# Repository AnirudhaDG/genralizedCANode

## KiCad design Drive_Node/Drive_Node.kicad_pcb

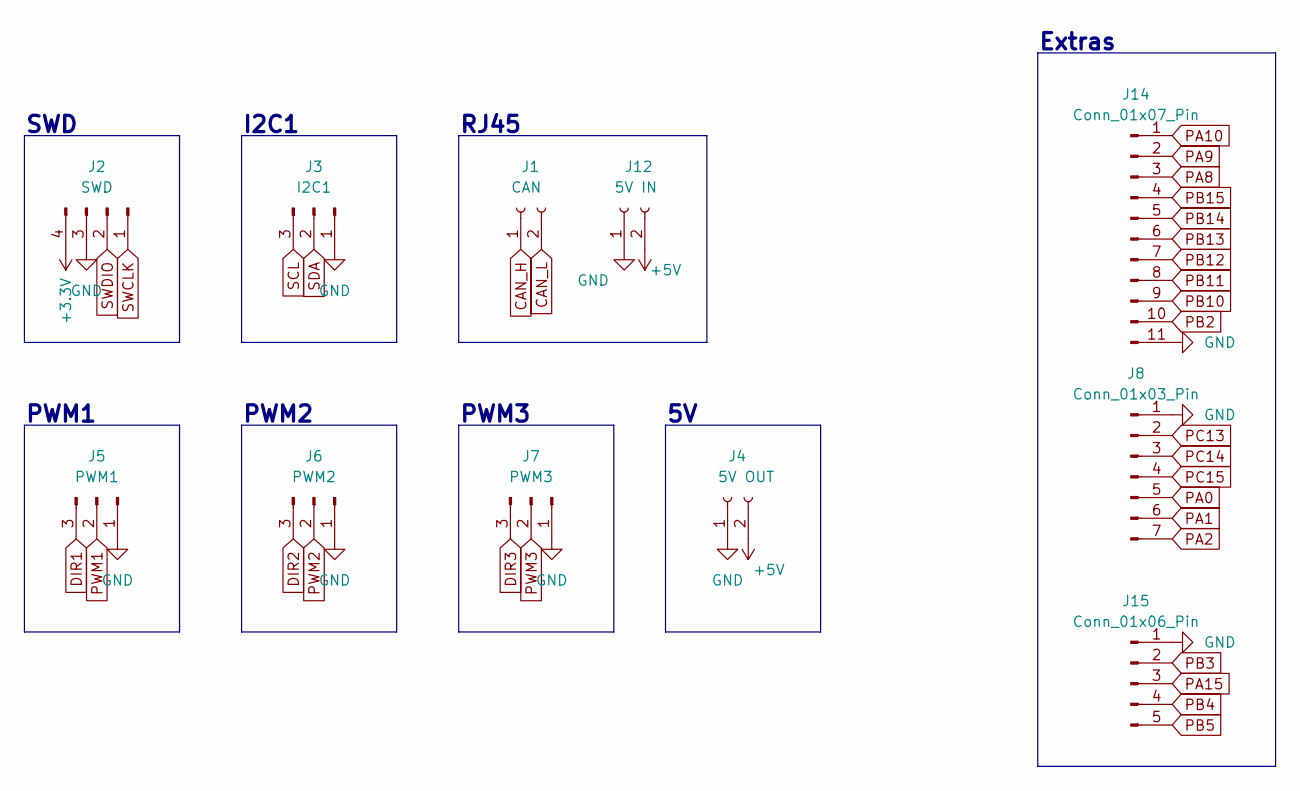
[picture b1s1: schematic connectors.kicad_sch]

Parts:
J1: CAN; LongSolderPad
J2: SWD; PinHeader_1x04_P2.54mm_Vertical
J3: I2C1; JST_PH_B3B-PH-K_1x03_P2.00mm_Vertical
J4: 5V OUT; JST_PH_B2B-PH-K_1x02_P2.00mm_Vertical
J5: PWM1; JST_PH_B3B-PH-K_1x03_P2.00mm_Vertical
J6: PWM2; JST_PH_B3B-PH-K_1x03_P2.00mm_Vertical
J7: PWM3; JST_PH_B3B-PH-K_1x03_P2.00mm_Vertical
J8: Conn_01x03_Pin; PinHeader_1x07_P2.54mm_Vertical
J12: 5V IN; LongSolderPad
J14: Conn_01x07_Pin; PinHeader_1x11_P2.54mm_Vertical
J15: Conn_01x06_Pin; PinHeader_1x05_P2.54mm_Vertical

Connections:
+3.3V: J2.4; also elsewhere on the board
+5V: J4.2, J12.2; also elsewhere on the board
CAN_H: J1.1; also elsewhere on the board
CAN_L: J1.2; also elsewhere on the board
DIR1: J5.3; also elsewhere on the board
DIR2: J6.3; also elsewhere on the board
DIR3: J7.3; also elsewhere on the board
GND: J2.3, J3.1, J4.1, J5.1, J6.1, J7.1, J8.1, J12.1, J14.11, J15.1; also elsewhere on the board
PA0: J8.5; also elsewhere on the board
PA1: J8.6; also elsewhere on the board
PA2: J8.7; also elsewhere on the board
PA8: J14.3; also elsewhere on the board
PA9: J14.2; also elsewhere on the board
PA10: J14.1; also elsewhere on the board
PA15: J15.3; also elsewhere on the board
PB2: J14.10; also elsewhere on the board
PB3: J15.2; also elsewhere on the board
PB4: J15.4; also elsewhere on the board
PB5: J15.5; also elsewhere on the board
PB10: J14.9; also elsewhere on the board
PB11: J14.8; also elsewhere on the board
PB12: J14.7; also elsewhere on the board
PB13: J14.6; also elsewhere on the board
PB14: J14.5; also elsewhere on the board
PB15: J14.4; also elsewhere on the board
PC13: J8.2; also elsewhere on the board
PC14: J8.3; also elsewhere on the board
PC15: J8.4; also elsewhere on the board
PWM1: J5.2; also elsewhere on the board
PWM2: J6.2; also elsewhere on the board
PWM3: J7.2; also elsewhere on the board
SCL: J3.3; also elsewhere on the board
SDA: J3.2; also elsewhere on the board
SWCLK: J2.1; also elsewhere on the board
SWDIO: J2.2; also elsewhere on the board

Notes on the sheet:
PWM1
SWD
PWM2
Extras
I2C1
PWM3
RJ45

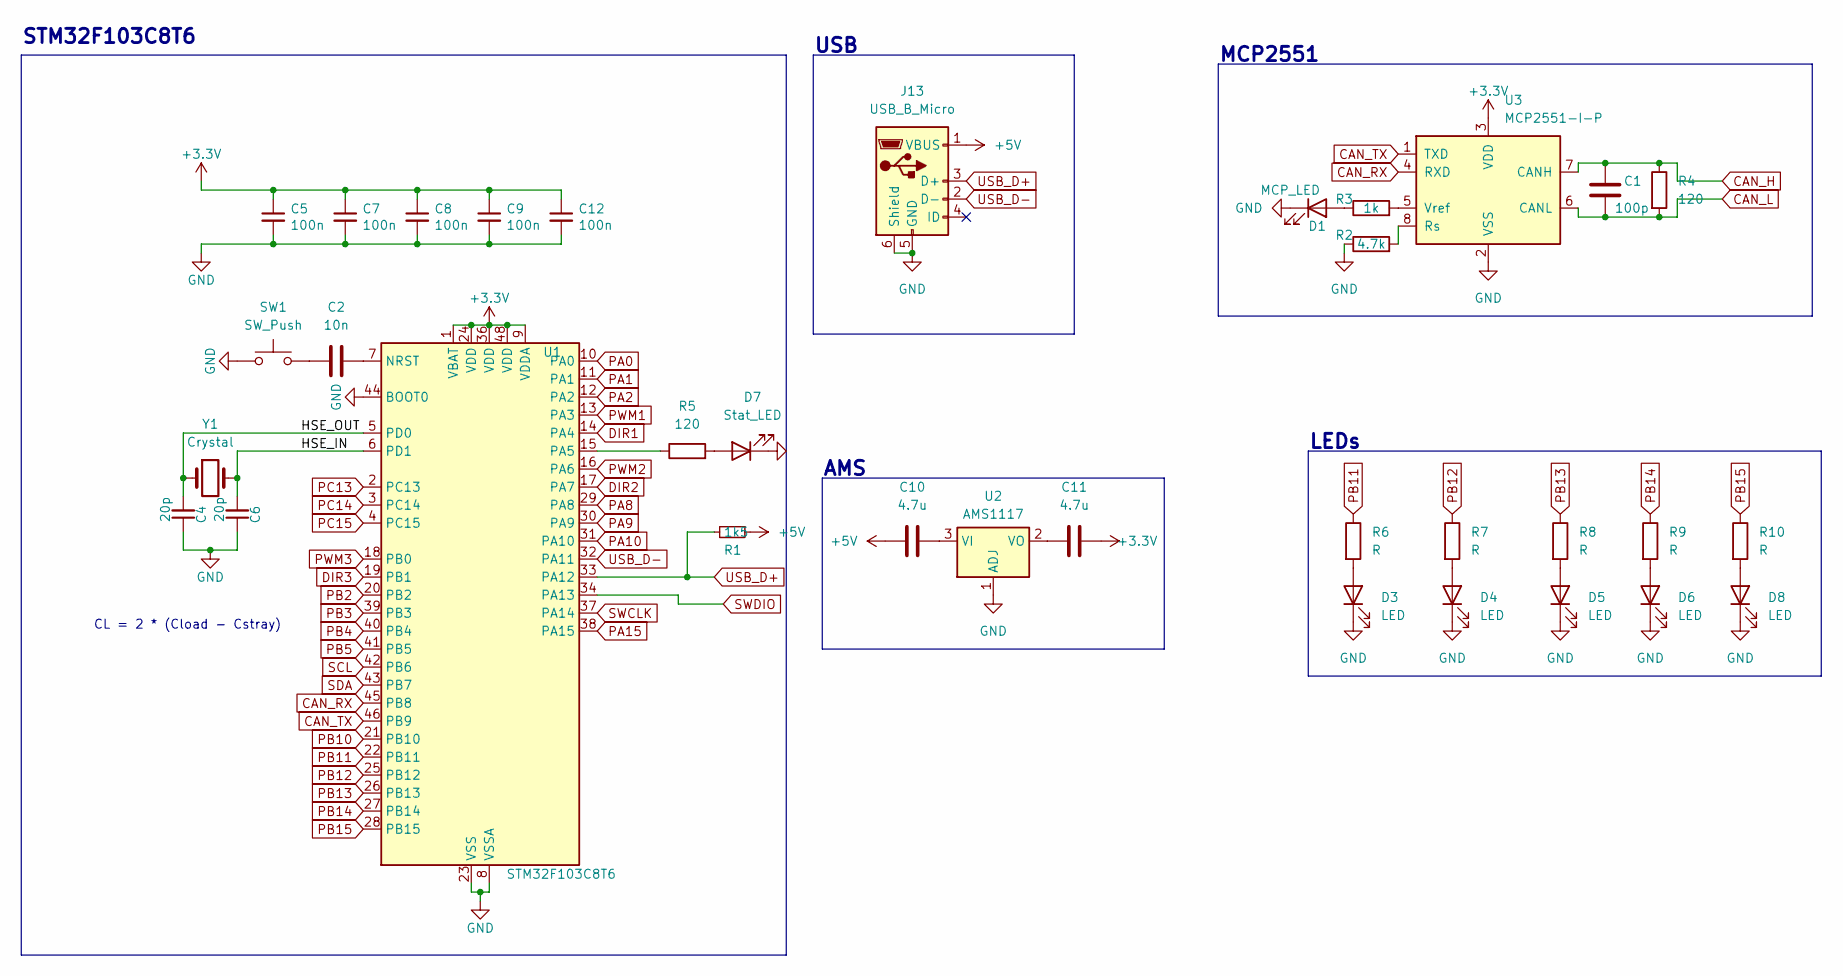
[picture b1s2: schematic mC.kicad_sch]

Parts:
C1: 100p; C_0805_2012Metric
C2: 10n; C_0805_2012Metric
C4, C6: 20p; C_0805_2012Metric; LCSC Part # C1570
C5, C7, C8, C9, C12: 100n; C_0805_2012Metric; LCSC Part # C1525
C10, C11: 4.7u; C_0805_2012Metric
D1: MCP_LED; LED_0805_2012Metric
D3, D4, D5, D6, D8: LED; LED_0805_2012Metric
D7: Stat_LED; LED_0805_2012Metric
J13: USB_B_Micro; USB_Micro-B_Wuerth_629105150521
R1: 1k5; R_0805_2012Metric; LCSC Part # C25867
R2: 4.7k; R_0805_2012Metric
R3: 1k; R_0805_2012Metric
R4, R5: 120; R_0805_2012Metric
R6, R7, R8, R9, R10: R; R_0805_2012Metric
SW1: SW_Push; SW_PUSH_6mm_H5mm
U1: STM32F103C8T6; LQFP-48_7x7mm_P0.5mm; LCSC Part # C8734
U2: AMS1117; SOT-223-3_TabPin2
U3: MCP2551-I-P; DIP-8_W7.62mm
Y1: Crystal; Crystal_HC49-U_Vertical

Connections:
+3.3V: C5.1, C7.1, C8.1, C9.1, C11.2, C12.1, U1.1 (VBAT), U1.9 (VDDA), U1.24 (VDD), U1.36 (VDD), U1.48 (VDD), U3.3 (VDD); also elsewhere on the board
+5V: C10.1, J13.1 (VBUS), R1.1; also elsewhere on the board
/Microcontroller+USB/HSE_IN: C6.2, U1.6 (PD1), Y1.2
/Microcontroller+USB/HSE_OUT: C4.2, U1.5 (PD0), Y1.1
CAN_H: C1.1, R4.1, U3.7 (CANH); also elsewhere on the board
CAN_L: C1.2, R4.2, U3.6 (CANL); also elsewhere on the board
CAN_RX: U1.45 (PB8), U3.4 (RXD)
CAN_TX: U1.46 (PB9), U3.1 (TXD)
DIR1: U1.14 (PA4); also elsewhere on the board
DIR2: U1.17 (PA7); also elsewhere on the board
DIR3: U1.19 (PB1); also elsewhere on the board
GND: C4.1, C5.2, C6.1, C7.2, C8.2, C9.2, C12.2, D1.1 (K), D3.1 (K), D4.1 (K), D5.1 (K), D6.1 (K), D7.1 (K), D8.1 (K), J13.5 (GND), J13.6 (Shield), R2.1, SW1.1, U1.8 (VSSA), U1.23 (VSS), U1.35 (VSS), U1.44 (BOOT0), U1.47 (VSS), U2.1 (ADJ), U3.2 (VSS); also elsewhere on the board
unnamed: C2.2, SW1.2
unnamed: D1.2 (A), R3.1
unnamed: D3.2 (A), R6.2
unnamed: D4.2 (A), R7.2
unnamed: D5.2 (A), R8.2
unnamed: D6.2 (A), R9.2
unnamed: D7.2 (A), R5.2
unnamed: D8.2 (A), R10.2
unnamed: C2.1, U1.7 (NRST)
unnamed: R5.1, U1.15 (PA5)
unnamed: C10.2, U2.3 (VI)
unnamed: C11.1, U2.2 (VO)
unnamed: R2.2, U3.8 (Rs)
unnamed: R3.2, U3.5 (Vref)
PA0: U1.10 (PA0); also elsewhere on the board
PA1: U1.11 (PA1); also elsewhere on the board
PA2: U1.12 (PA2); also elsewhere on the board
PA8: U1.29 (PA8); also elsewhere on the board
PA9: U1.30 (PA9); also elsewhere on the board
PA10: U1.31 (PA10); also elsewhere on the board
PA15: U1.38 (PA15); also elsewhere on the board
PB2: U1.20 (PB2); also elsewhere on the board
PB3: U1.39 (PB3); also elsewhere on the board
PB4: U1.40 (PB4); also elsewhere on the board
PB5: U1.41 (PB5); also elsewhere on the board
PB10: U1.21 (PB10); also elsewhere on the board
PB11: R6.1, U1.22 (PB11); also elsewhere on the board
PB12: R7.1, U1.25 (PB12); also elsewhere on the board
PB13: R8.1, U1.26 (PB13); also elsewhere on the board
PB14: R9.1, U1.27 (PB14); also elsewhere on the board
PB15: R10.1, U1.28 (PB15); also elsewhere on the board
PC13: U1.2 (PC13); also elsewhere on the board
PC14: U1.3 (PC14); also elsewhere on the board
PC15: U1.4 (PC15); also elsewhere on the board
PWM1: U1.13 (PA3); also elsewhere on the board
PWM2: U1.16 (PA6); also elsewhere on the board
PWM3: U1.18 (PB0); also elsewhere on the board
SCL: U1.42 (PB6); also elsewhere on the board
SDA: U1.43 (PB7); also elsewhere on the board
SWCLK: U1.37 (PA14); also elsewhere on the board
SWDIO: U1.34 (PA13); also elsewhere on the board
USB_D+: J13.3 (D+), R1.2, U1.33 (PA12)
USB_D-: J13.2 (D-), U1.32 (PA11)

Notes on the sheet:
MCP2551
STM32F103C8T6
AMS
LEDs
USB
CL = 2 * (Cload - Cstray)

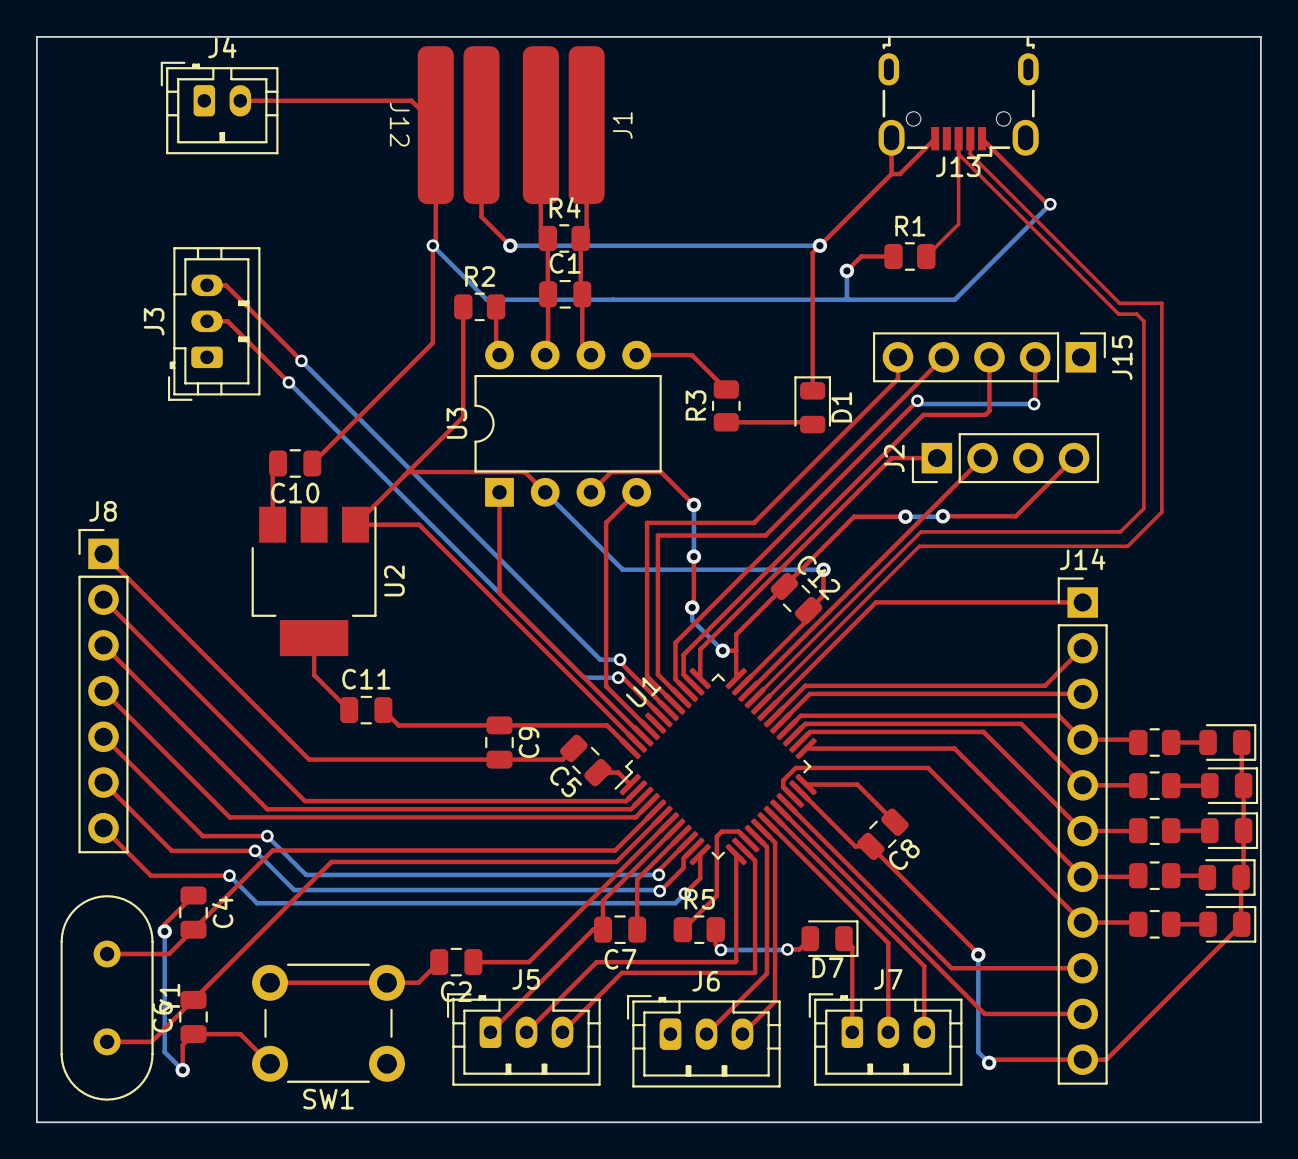
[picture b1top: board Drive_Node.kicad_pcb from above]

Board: 2 copper layers, 68.0 x 60.3 mm, 45 parts (0 on the bottom side), 55 nets.

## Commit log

2024-07-05 CAN V01
